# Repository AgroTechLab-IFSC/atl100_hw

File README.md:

# ATL-100 (Hardware)

**ATL-100** is a multiparametric station developed by <a href="https://agrotechlab.lages.ifsc.edu.br">AgroTechLab (*Agribusiness Technology Development Laboratory*)</a> of <a href="https://www.ifsc.edu.br">IFSC (*Federal Institute of Santa Catarina*)</a>.

It can be used as meteorological station, agrometeorological station, hydrological station, aquaculture station, tide gauge station or fire monitoring station (forest or urban environment).

It is a PTH (*Plated-Through-Hole*) project based on the ESP32-S3 MCU that aims to be easy to produce and low cost, so it uses COTS (*Commercial Off-The-Shelf*) hardware.

## Features

The current version of the ATL-100 has the following features:

### Main Board

 - Power Supply (XL4005)
   - Input: 10V ~ 30V;
   - Current: 2.5A (typ.) / 5A (max. with heat sink);
   - Efficiency: 90%
   - Frequency: 300KHz
 - Power Supply Sensor
   - Voltage Divider (30V -> 3.33V);
 - MCU (ESP32-S3)
   - RISC 32 bits 240MHz dual-core;
   - 16Mb Flash;
   - 512Kb SRAM;
   - 16Kb SRAM in RTC;
   - 8Mb PSRAM;
   - 384Kb ROM;
 - RS-485 (HW-519)
   - TTL to RS-485 converter;
   - Modbus-RTU protocol;
   - Used to connect HaliSense TH-EC-PH-NPK soil sensor:
     - Soil temperature (-40 ~ 80 ℃);
     - Soil moisture (0 ~ 100 %);
     - Soil electroconductivity (0 ~ 20.000 us/cm);
     - Soil pH (3 ~ 9 pH);
     - Soil nitrogen, phosphorus, potassium (1 ~ 1999 mg/Kg or mg/L)
 - Windsock (voltage drop based);
 - Anemometer (pulse counter based);
 - Pluviometer (pulse counter based);
 - Air sensor (BME-280)
   - Air Temperature (-40 ~ 85 ℃);
   - Air Humidity (0 ~ 100 %);
   - Atmospheric Pressure (300 ~ 1100 hPa);

### ADC Board
 - ADC (ADS1115)
   - 16 bits resolution;
   - 4 channels (4mA ~ 20mA / 0V ~ 10V);

## 3D Images

<br><hr><p style="text-align: center;">All rights reserved. &copy; Since 2020.<br><b><a href="https://agrotechlab.lages.ifsc.edu.br/">AgroTechLab (<i>Agribusiness Technology Development Laboratory</i>)</a></b><br>
<b><a href="https://ifsc.edu.br/web/campus-lages">IFSC (<i>Federal Institute of Santa Catarina</i>) - Campus Lages</a></b><br>
225 Heitor Vila Lobos St., São Francisco<br>
Lages/SC - Brazil<br>
88506-400</p>

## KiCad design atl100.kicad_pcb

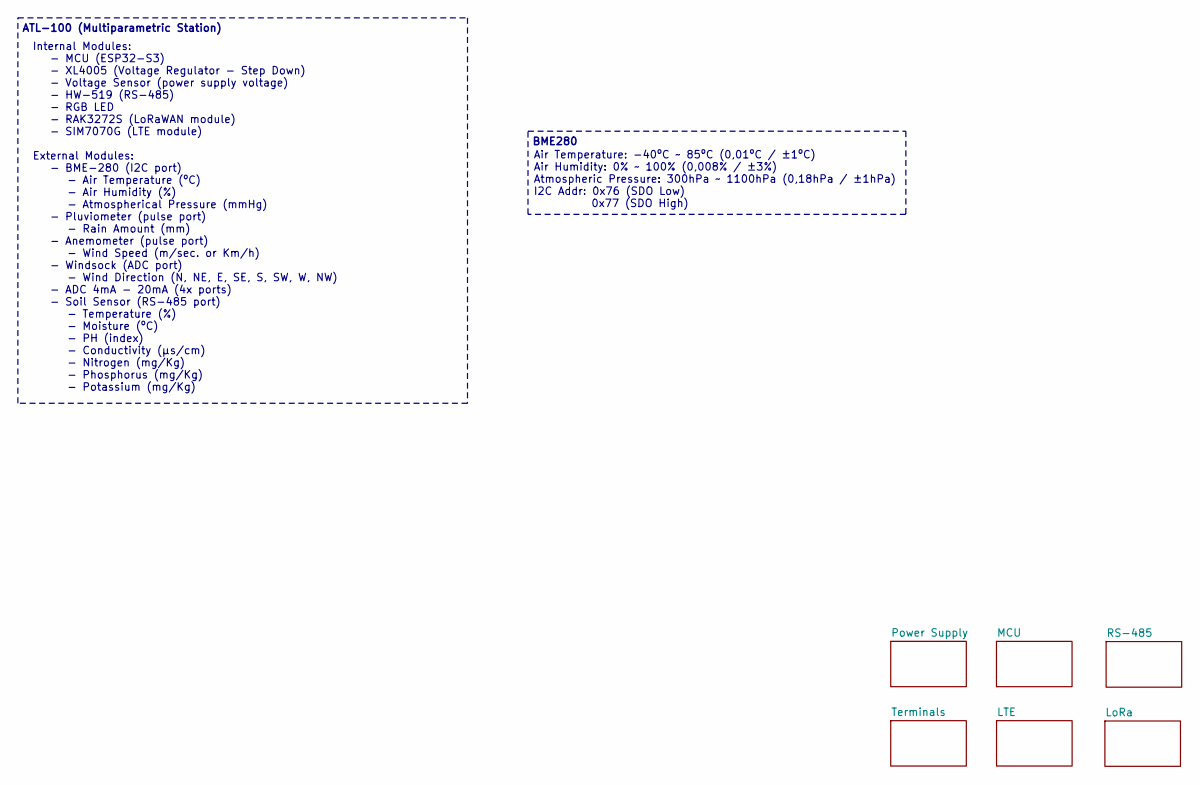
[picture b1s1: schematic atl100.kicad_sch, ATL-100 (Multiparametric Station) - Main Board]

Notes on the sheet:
BME280
Air Temperature: -40ºC ~ 85ºC (0,01ºC / ±1ºC) Air Humidity: 0% ~ 100% (0,008% / ±3%) Atmospheric Pressure: 300hPa ~ 1100hPa (0,18hPa / ±1hPa) I2C Addr: 0x76 (SDO Low) 0x77 (SDO High)
Internal Modules: - MCU (ESP32-S3) - XL4005 (Voltage Regulator - Step Down) - Voltage Sensor (power supply voltage) - HW-519 (RS-485) - RGB LED - RAK3272S (LoRaWAN module) - SIM7070G (LTE module) External Modules: - BME-280 (I2C port) - Air Temperature (ºC) - Air Humidity (%) - Atmospherical Pressu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
ATL-100 (Multiparametric Station)

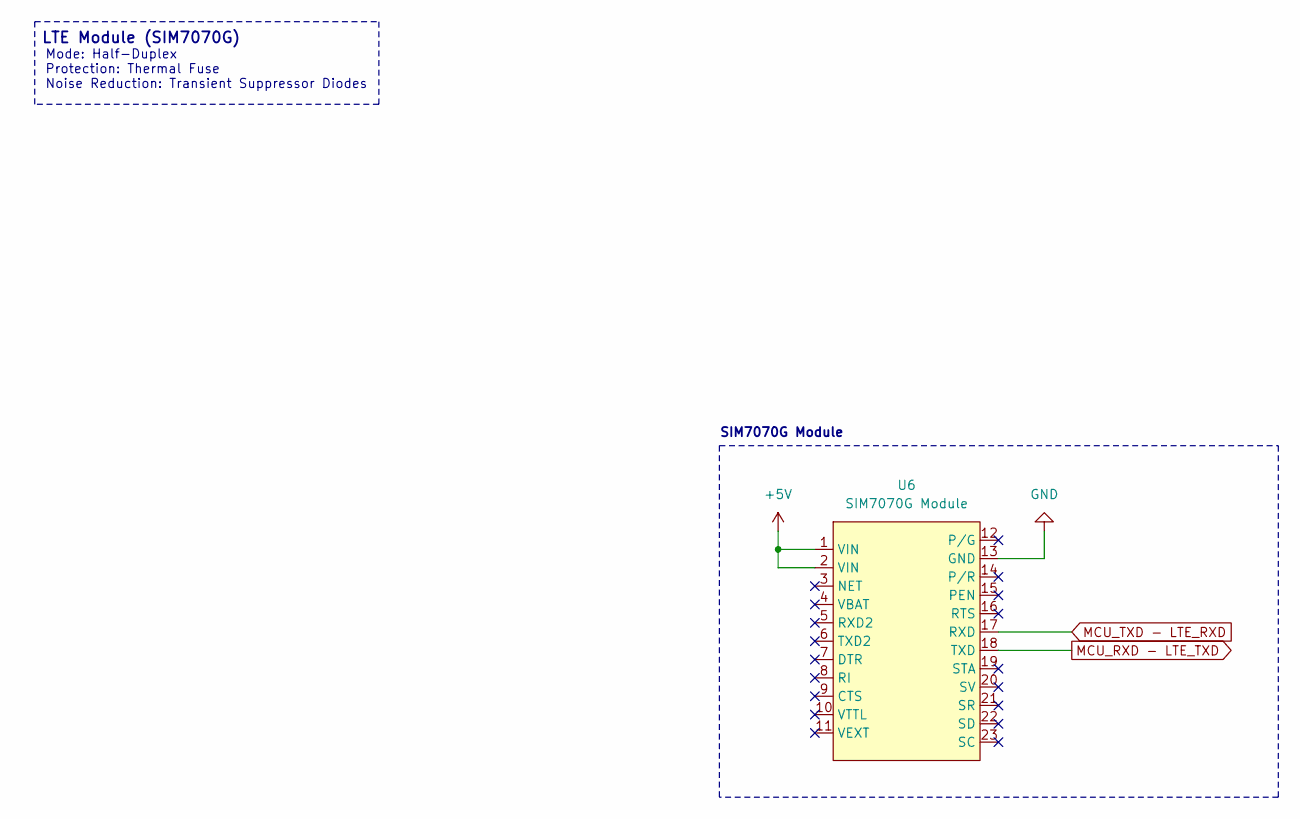
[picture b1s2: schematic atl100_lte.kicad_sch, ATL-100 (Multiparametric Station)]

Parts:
U6: SIM7070G Module; Part Number OEM

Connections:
+5V: U6.1 (VIN), U6.2 (VIN); also elsewhere on the board
GND: U6.12 (P/G), U6.13 (GND); also elsewhere on the board
LTE_PEN: U6.15 (PEN); also elsewhere on the board

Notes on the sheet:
LTE Module (SIM7070G)
SIM7070G Module
Mode: Half-Duplex Protection: Thermal Fuse Noise Reduction: Transient Suppressor Diodes

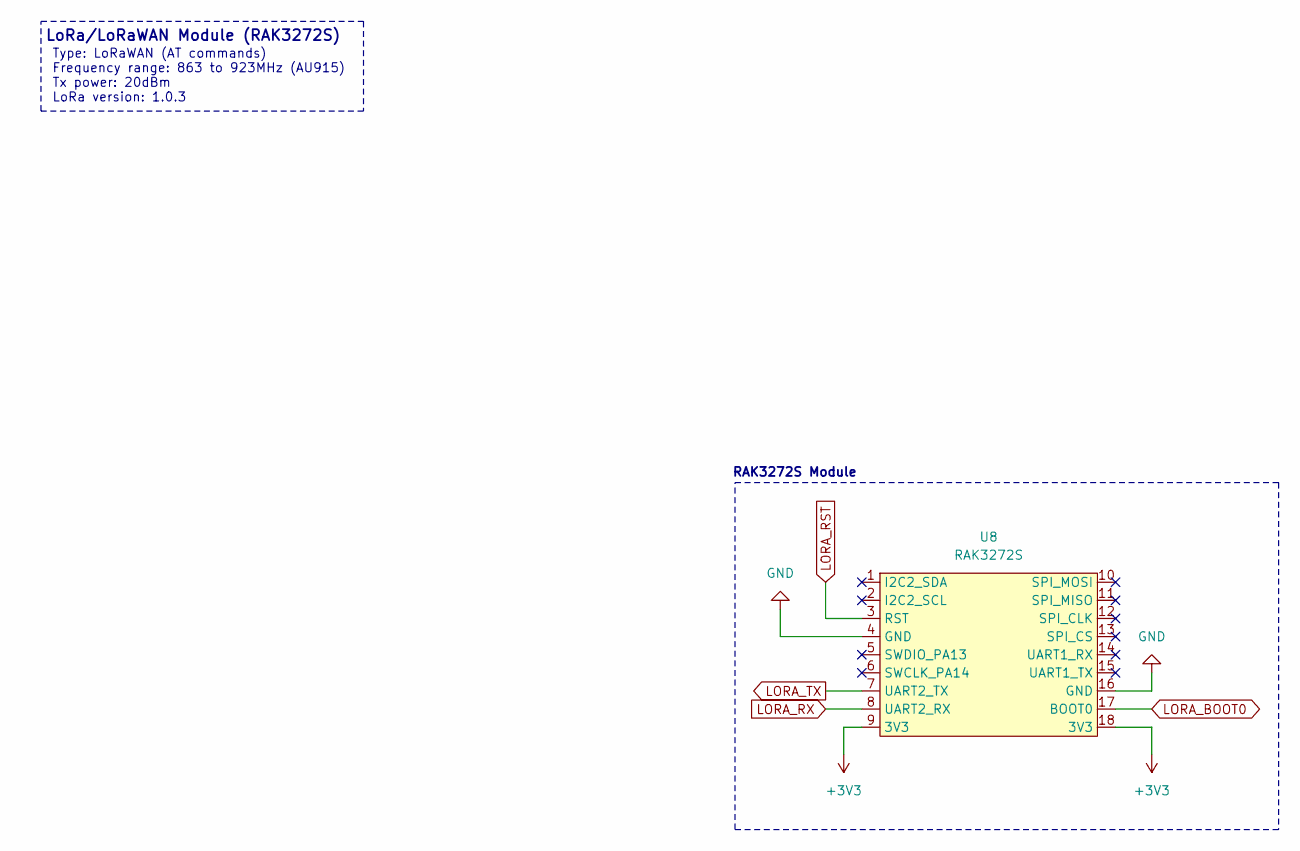
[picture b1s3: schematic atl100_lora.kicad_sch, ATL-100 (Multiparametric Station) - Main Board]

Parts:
U8: RAK3272S

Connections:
+3V3: U8.9 (3V3), U8.18 (3V3); also elsewhere on the board
GND: U8.4 (GND), U8.16 (GND); also elsewhere on the board
LORA_BOOT0: U8.17 (BOOT0); also elsewhere on the board
LORA_RST: U8.3 (RST); also elsewhere on the board
LORA_RX: U8.8 (UART2_RX); also elsewhere on the board
LORA_TX: U8.7 (UART2_TX); also elsewhere on the board

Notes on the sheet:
LoRa/LoRaWAN Module (RAK3272S)
Type: LoRaWAN (AT commands) Frequency range: 863 to 923MHz (AU915) Tx power: 20dBm LoRa version: 1.0.3
RAK3272S Module

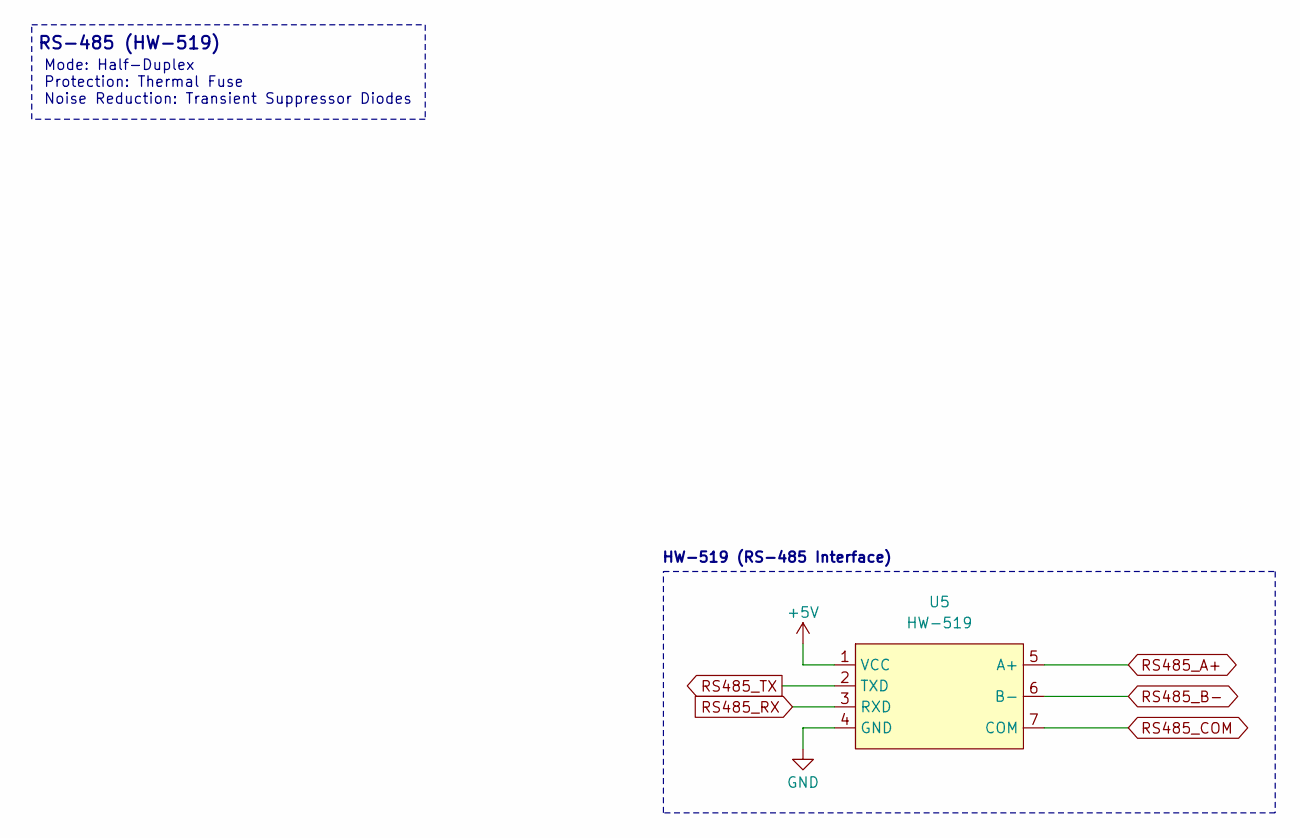
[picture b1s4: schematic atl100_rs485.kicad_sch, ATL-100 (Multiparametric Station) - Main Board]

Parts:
U5: HW-519

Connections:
+5V: U5.1 (VCC); also elsewhere on the board
GND: U5.4 (GND); also elsewhere on the board
RS485_A+: U5.5 (A+); also elsewhere on the board
RS485_B-: U5.6 (B-); also elsewhere on the board
RS485_COM: U5.7 (COM); also elsewhere on the board
RS485_RX: U5.3 (RXD); also elsewhere on the board
RS485_TX: U5.2 (TXD); also elsewhere on the board

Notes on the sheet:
RS-485 (HW-519)
Mode: Half-Duplex Protection: Thermal Fuse Noise Reduction: Transient Suppressor Diodes
HW-519 (RS-485 Interface)

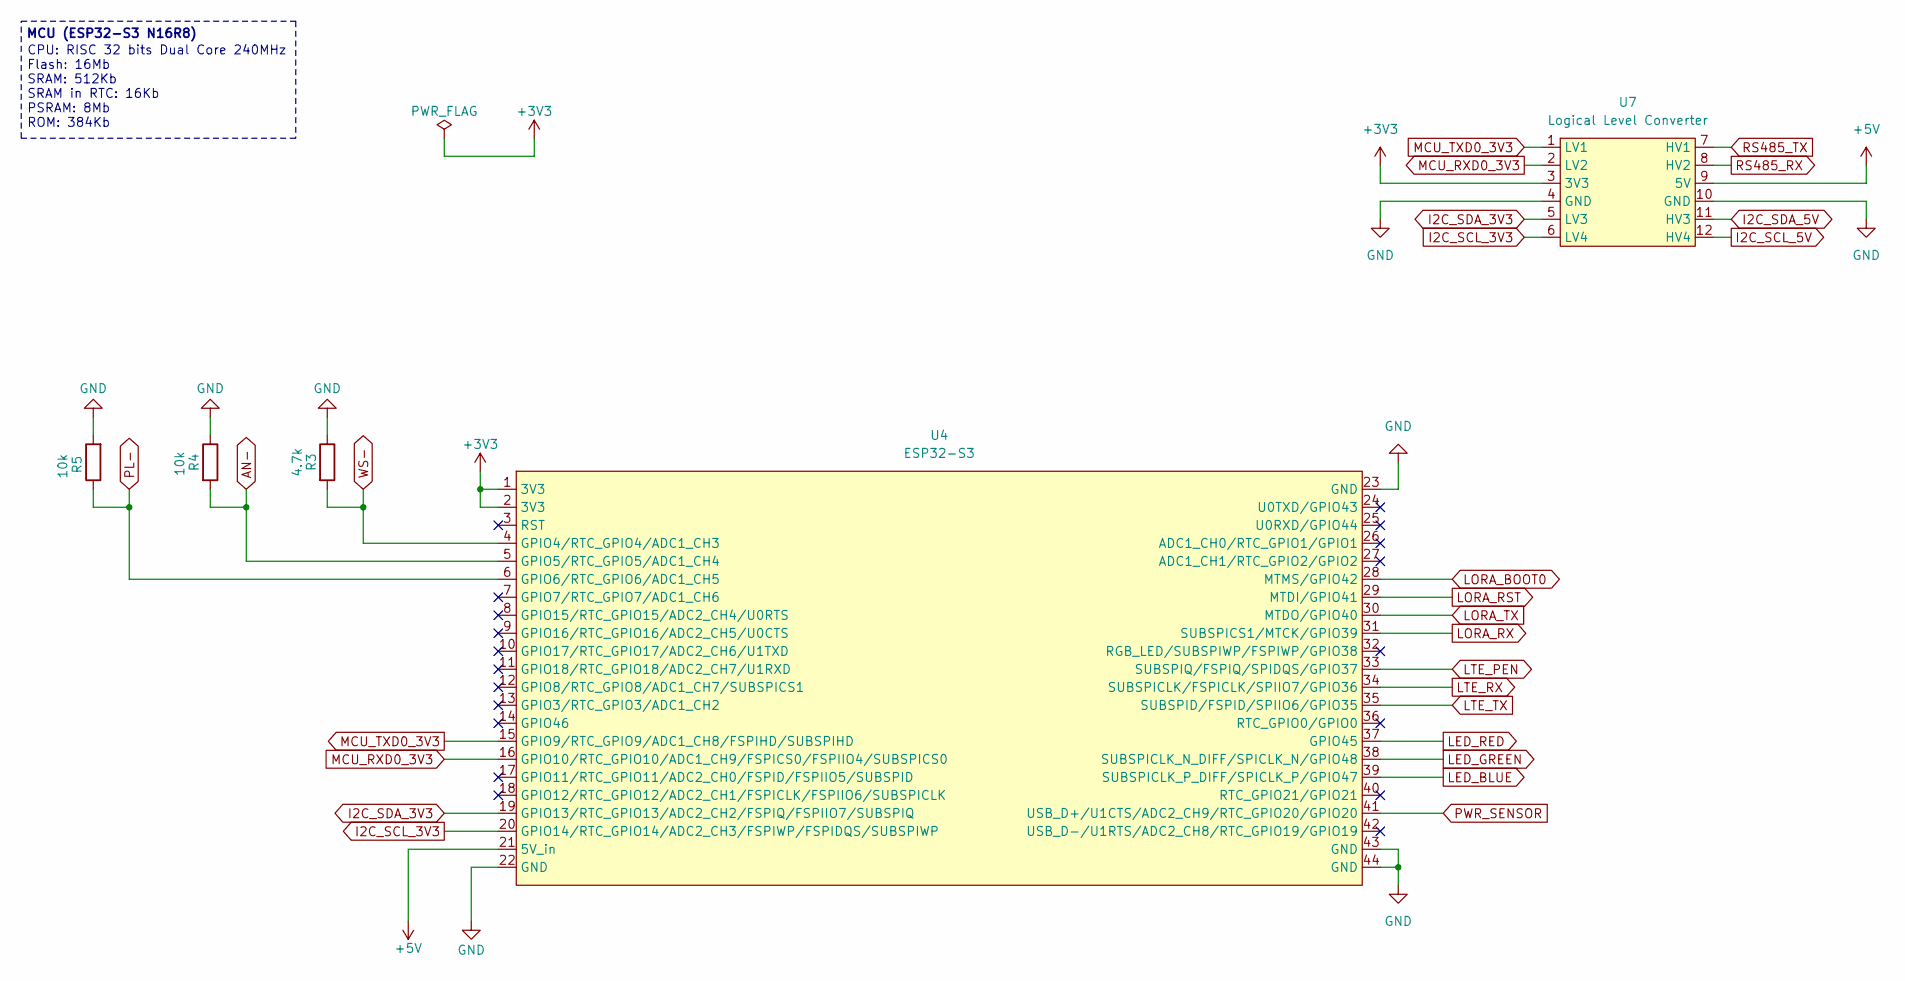
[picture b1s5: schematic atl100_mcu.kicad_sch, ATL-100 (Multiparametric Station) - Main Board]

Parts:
R3: 4.7k; R_Axial_DIN0207_L6.3mm_D2.5mm_P10.16mm_Horizontal; Part Number Std
R4, R5: 10k; R_Axial_DIN0207_L6.3mm_D2.5mm_P10.16mm_Horizontal; Part Number Std
U4: ESP32-S3; ESP32-S3 N16R8
U7: Logical Level Converter

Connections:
+3V3: U4.1 (3V3), U4.2 (3V3), U7.3 (3V3); also elsewhere on the board
+5V: U4.21 (5V_in), U7.9 (5V); also elsewhere on the board
AN-: R4.2, U4.5 (GPIO5/RTC_GPIO5/ADC1_CH4); also elsewhere on the board
GND: R3.1, R4.1, R5.2, U4.22 (GND), U4.23 (GND), U4.43 (GND), U4.44 (GND), U7.4 (GND), U7.10 (GND); also elsewhere on the board
I2C_SCL_3V3: U4.20 (GPIO14/RTC_GPIO14/ADC2_CH3/FSPIWP/FSPID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), U7.6 (LV4)
I2C_SCL_5V: U7.12 (HV4); also elsewhere on the board
I2C_SDA_3V3: U4.19 (GPIO13/RTC_GPIO13/ADC2_CH2/FSPIQ/FSPIIO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), U7.5 (LV3)
I2C_SDA_5V: U7.11 (HV3); also elsewhere on the board
LED_BLUE: U4.39 (SUBSPICLK_P_DIFF/SPICLK_P/GPIO47); also elsewhere on the board
LED_GREEN: U4.38 (SUBSPICLK_N_DIFF/SPICLK_N/GPIO48); also elsewhere on the board
LED_RED: U4.37 (GPIO45); also elsewhere on the board
LORA_BOOT0: U4.28 (MTMS/GPIO42); also elsewhere on the board
LORA_RST: U4.29 (MTDI/GPIO41); also elsewhere on the board
LORA_RX: U4.31 (SUBSPICS1/MTCK/GPIO39); also elsewhere on the board
LORA_TX: U4.30 (MTDO/GPIO40); also elsewhere on the board
LTE_PEN: U4.33 (SUBSPIQ/FSPIQ/SPIDQS/GPIO37); also elsewhere on the board
MCU_RXD0_3V3: U4.16 (GPIO10/RTC_GPIO10/ADC1_CH9/FSPICS0/FSPI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), U7.2 (LV2)
MCU_TXD0_3V3: U4.15 (GPIO9/RTC_GPIO9/ADC1_CH8/FSPIHD/SUBSPIHD), U7.1 (LV1)
PL-: R5.1, U4.6 (GPIO6/RTC_GPIO6/ADC1_CH5); also elsewhere on the board
PWR_SENSOR: U4.41 (USB_D+/U1CTS/ADC2_CH9/RTC_GPIO20/GPIO20); also elsewhere on the board
RS485_RX: U7.8 (HV2); also elsewhere on the board
RS485_TX: U7.7 (HV1); also elsewhere on the board
WS-: R3.2, U4.4 (GPIO4/RTC_GPIO4/ADC1_CH3); also elsewhere on the board

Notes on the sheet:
CPU: RISC 32 bits Dual Core 240MHz Flash: 16Mb SRAM: 512Kb SRAM in RTC: 16Kb PSRAM: 8Mb ROM: 384Kb
MCU (ESP32-S3 N16R8)

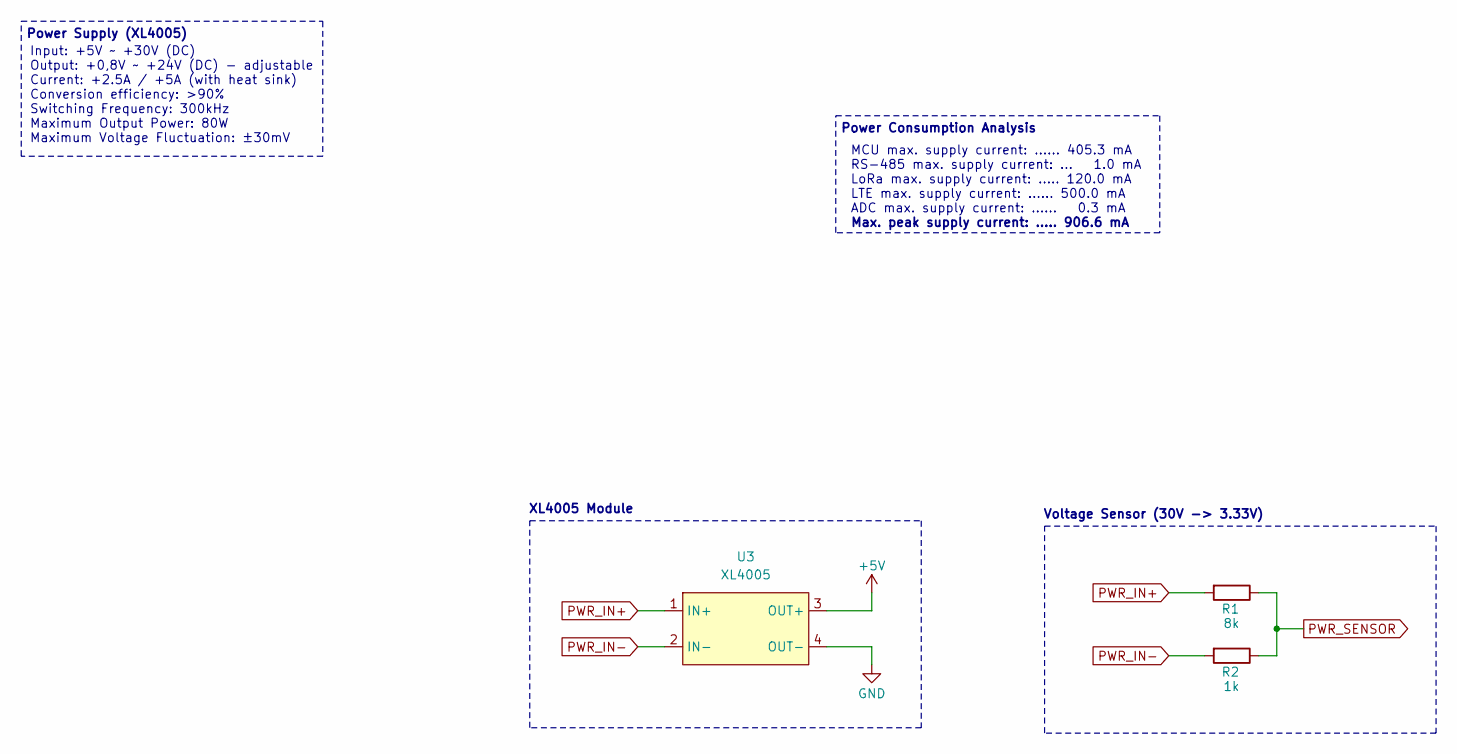
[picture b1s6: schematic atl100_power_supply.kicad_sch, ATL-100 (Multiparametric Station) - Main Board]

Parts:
R1: 8k; R_Axial_DIN0207_L6.3mm_D2.5mm_P10.16mm_Horizontal; Part Number Std
R2: 1k; R_Axial_DIN0207_L6.3mm_D2.5mm_P10.16mm_Horizontal; Part Number Std
U3: XL4005; Part Number Std

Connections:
+5V: U3.3 (OUT+); also elsewhere on the board
GND: U3.4 (OUT-); also elsewhere on the board
PWR_IN+: R1.2, U3.1 (IN+); also elsewhere on the board
PWR_IN-: R2.2, U3.2 (IN-); also elsewhere on the board
PWR_SENSOR: R1.1, R2.1; also elsewhere on the board

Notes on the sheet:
Voltage Sensor (30V -> 3.33V)
XL4005 Module
Max. peak supply current: ..... 906.6 mA
MCU max. supply current: ...... 405.3 mA RS-485 max. supply current: ... 1.0 mA LoRa max. supply current: ..... 120.0 mA LTE max. supply current: ...... 500.0 mA ADC max. supply current: ...... 0.3 mA
Input: +5V ~ +30V (DC) Output: +0,8V ~ +24V (DC) - adjustable Current: +2.5A / +5A (with heat sink) Conversion efficiency: >90% Switching Frequency: 300kHz Maximum Output Power: 80W Maximum Voltage Fluctuation: ±30mV
Power Consumption Analysis
Power Supply (XL4005)

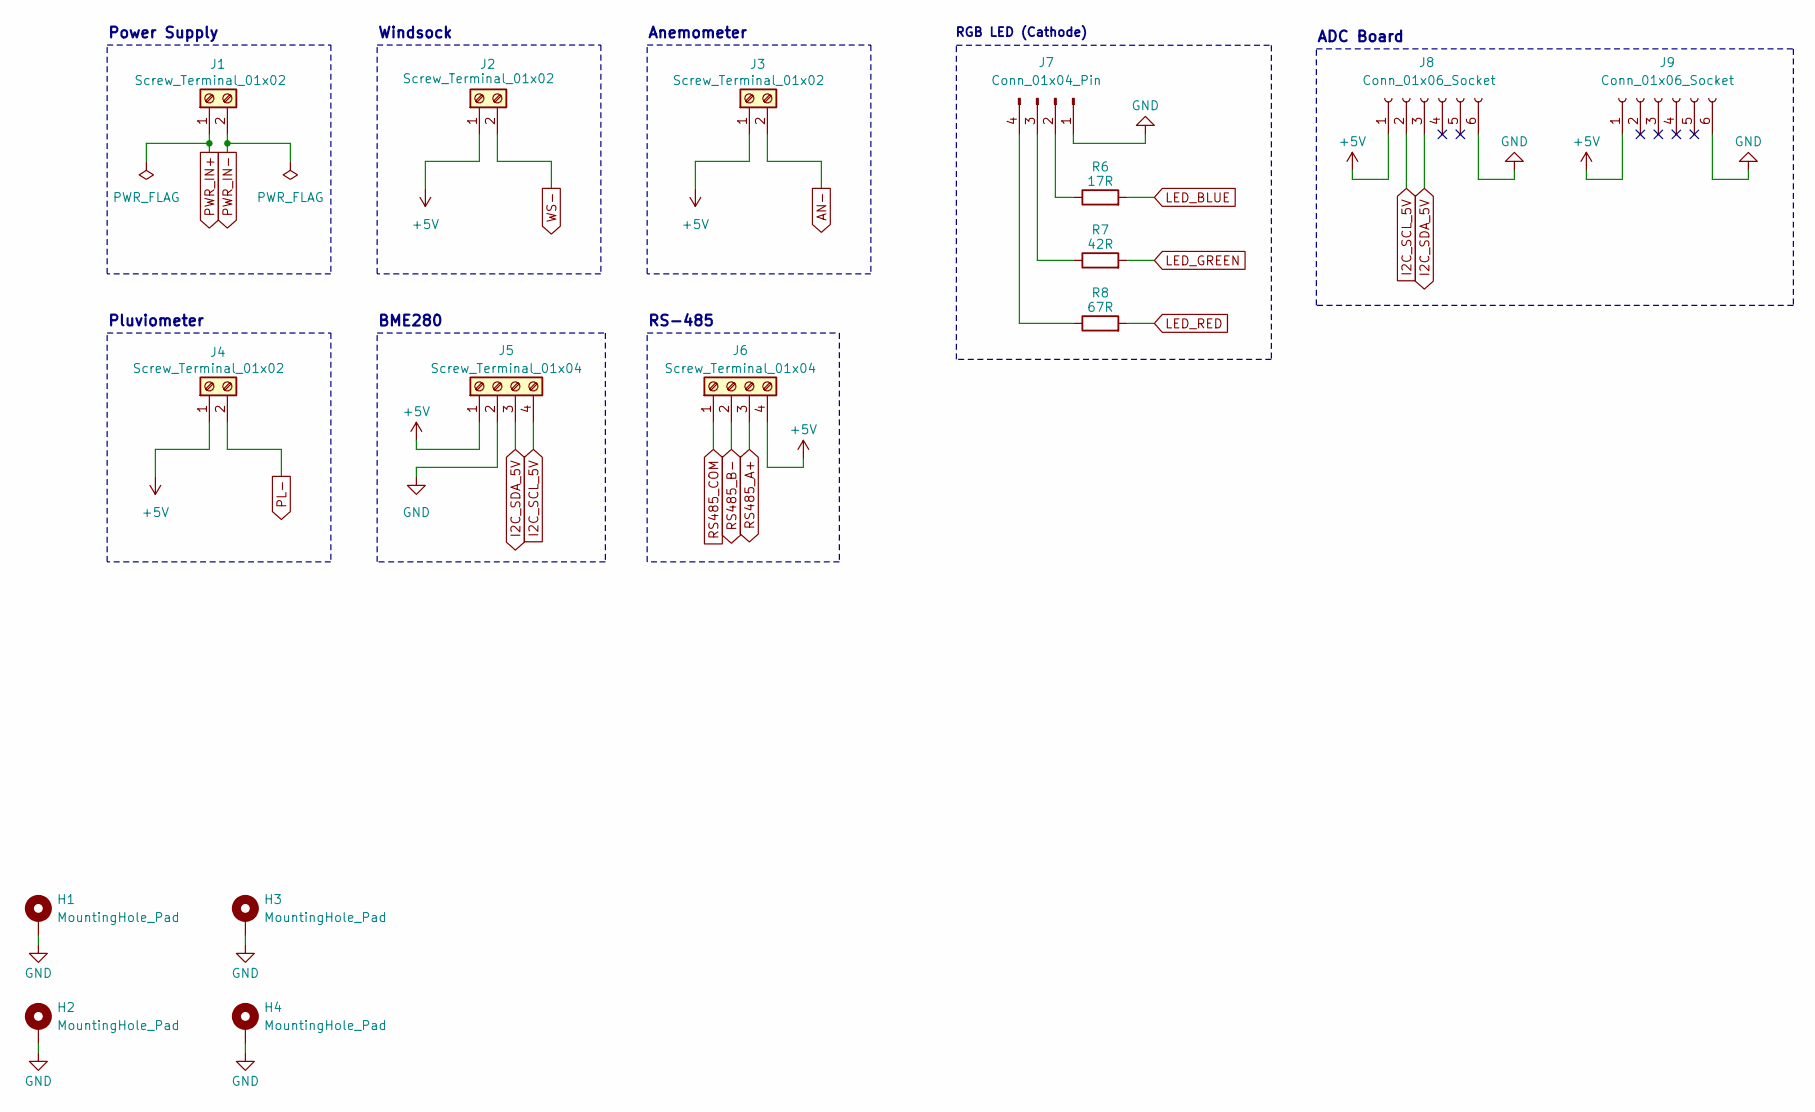
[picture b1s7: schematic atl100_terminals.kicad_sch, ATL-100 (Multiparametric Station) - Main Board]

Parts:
H1, H2, H3, H4: MountingHole_Pad; MountingHole_2.2mm_M2_Pad_Via
J1, J2, J3, J4: Screw_Terminal_01x02; TerminalBlock_Phoenix_MKDS-1,5-2-5.08_1x02_P5.08mm_Horizont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; Part Number Std
J5, J6: Screw_Terminal_01x04; TerminalBlock_Phoenix_MKDS-1,5-4-5.08_1x04_P5.08mm_Horizont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; Part Number Std
J7: Conn_01x04_Pin; PinHeader_1x04_P2.54mm_Horizontal
J8, J9: Conn_01x06_Socket; PinSocket_1x06_P2.54mm_Vertical
R6: 17R; R_Axial_DIN0207_L6.3mm_D2.5mm_P10.16mm_Horizontal; Part Number Std
R7: 42R; R_Axial_DIN0207_L6.3mm_D2.5mm_P10.16mm_Horizontal; Part Number Std
R8: 67R; R_Axial_DIN0207_L6.3mm_D2.5mm_P10.16mm_Horizontal; Part Number Std

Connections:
+5V: J2.1, J3.1, J4.1, J5.1, J6.4, J8.1, J9.1; also elsewhere on the board
AN-: J3.2; also elsewhere on the board
GND: H1.1, H2.1, H3.1, H4.1, J5.2, J7.1, J8.6, J9.6; also elsewhere on the board
I2C_SCL_5V: J5.4, J8.2; also elsewhere on the board
I2C_SDA_5V: J5.3, J8.3; also elsewhere on the board
LED_BLUE: R6.2; also elsewhere on the board
LED_GREEN: R7.2; also elsewhere on the board
LED_RED: R8.2; also elsewhere on the board
unnamed: J7.2, R6.1
unnamed: J7.3, R7.1
unnamed: J7.4, R8.1
PL-: J4.2; also elsewhere on the board
PWR_IN+: J1.1; also elsewhere on the board
PWR_IN-: J1.2; also elsewhere on the board
RS485_A+: J6.3; also elsewhere on the board
RS485_B-: J6.2; also elsewhere on the board
RS485_COM: J6.1; also elsewhere on the board
WS-: J2.2; also elsewhere on the board

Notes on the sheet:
Anemometer
Windsock
Pluviometer
ADC Board
Power Supply
BME280
RS-485
RGB LED (Cathode)

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
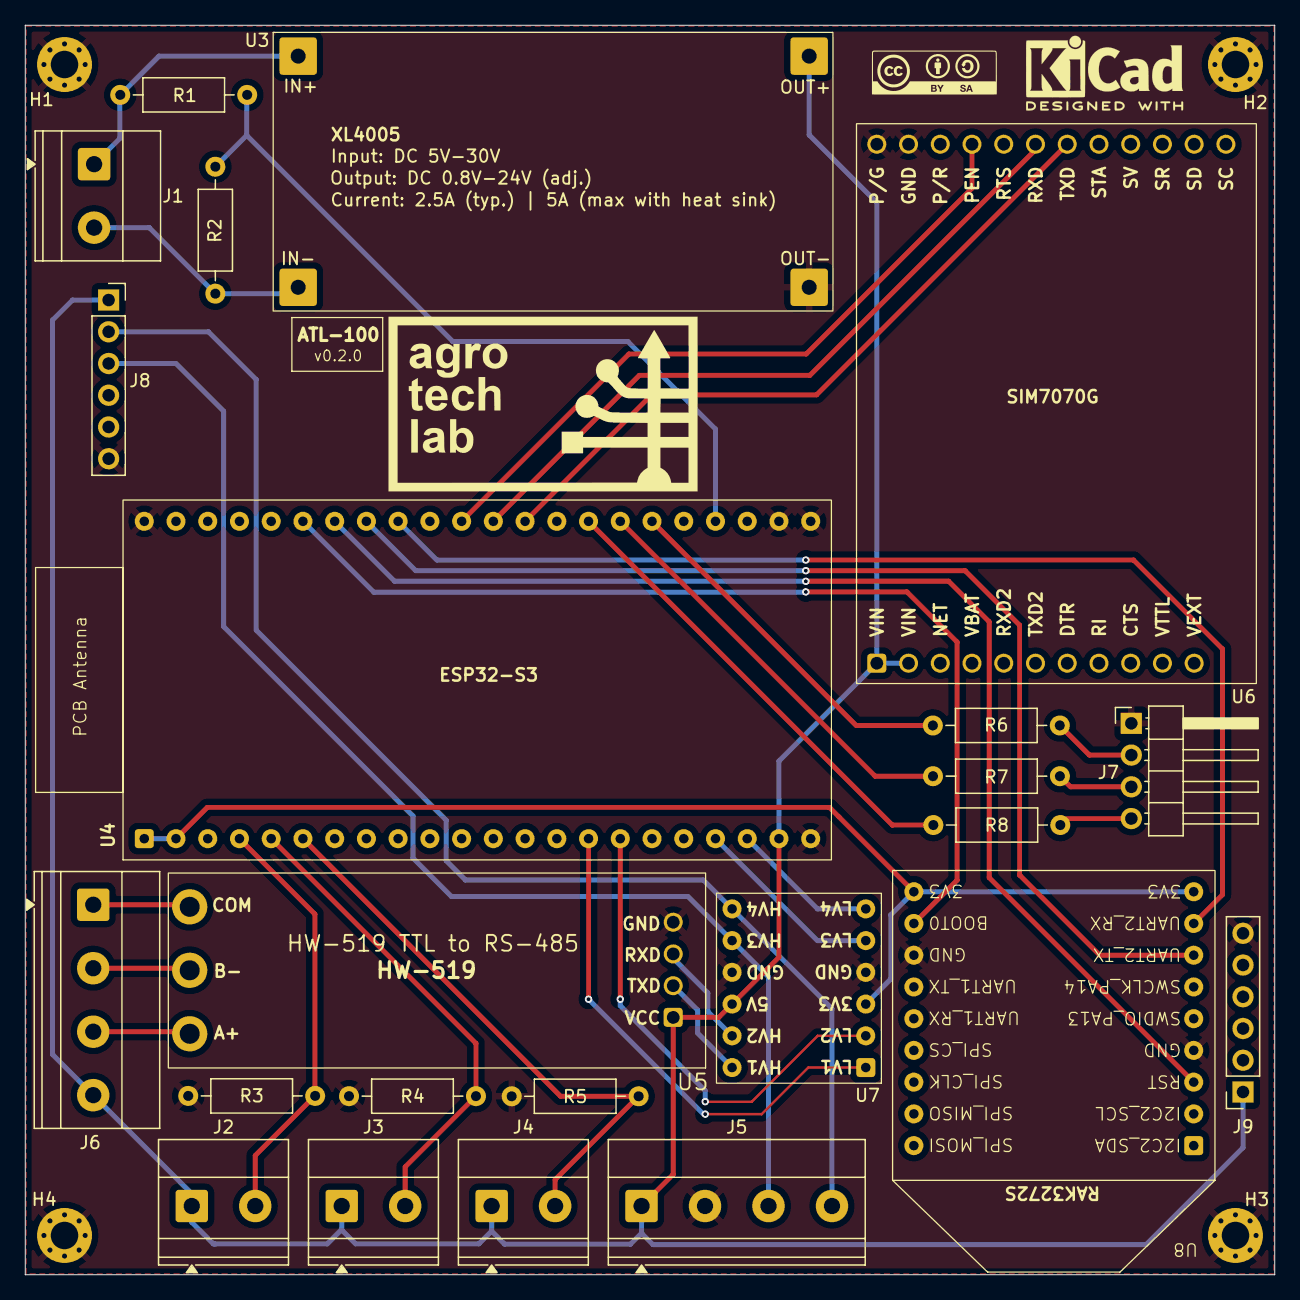
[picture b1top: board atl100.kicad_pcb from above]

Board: 2 copper layers, 100.0 x 100.0 mm, 30 parts (0 on the bottom side), 33 nets.

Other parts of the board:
agrotechlab_logo: Logo AgroTechLab
cc_by_sa_logo: Logo CC-BY-SA
kicad_logo: KiCad-Logo2_5mm_SilkScreen

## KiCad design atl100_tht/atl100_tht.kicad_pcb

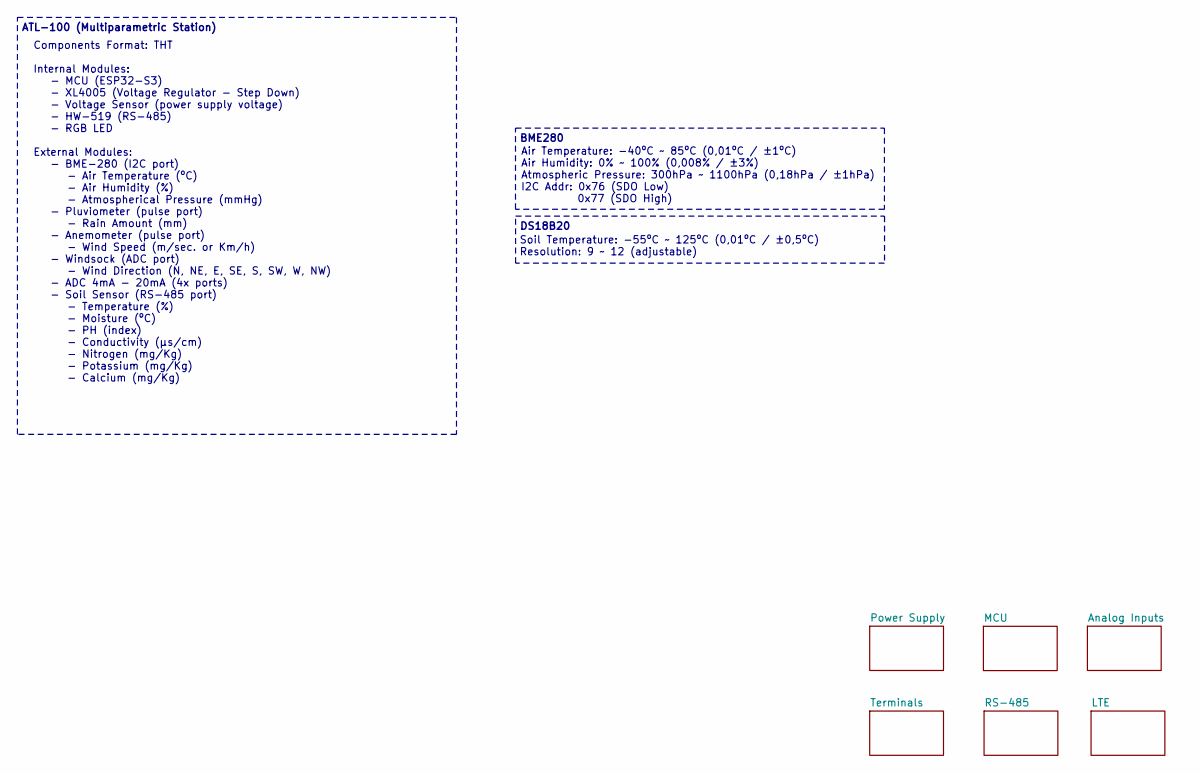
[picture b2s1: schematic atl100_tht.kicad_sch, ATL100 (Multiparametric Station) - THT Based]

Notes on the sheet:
Soil Temperature: -55ºC ~ 125ºC (0,01ºC / ±0,5ºC) Resolution: 9 ~ 12 (adjustable)
DS18B20
BME280
Air Temperature: -40ºC ~ 85ºC (0,01ºC / ±1ºC) Air Humidity: 0% ~ 100% (0,008% / ±3%) Atmospheric Pressure: 300hPa ~ 1100hPa (0,18hPa / ±1hPa) I2C Addr: 0x76 (SDO Low) 0x77 (SDO High)
Components Format: THT Internal Modules: - MCU (ESP32-S3) - XL4005 (Voltage Regulator - Step Down) - Voltage Sensor (power supply voltage) - HW-519 (RS-485) - RGB LED External Modules: - BME-280 (I2C port) - Air Temperature (ºC) - Air Humidity (%) - Atmospherical Pressure (mmHg) - Pluviometer (puls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
ATL-100 (Multiparametric Station)

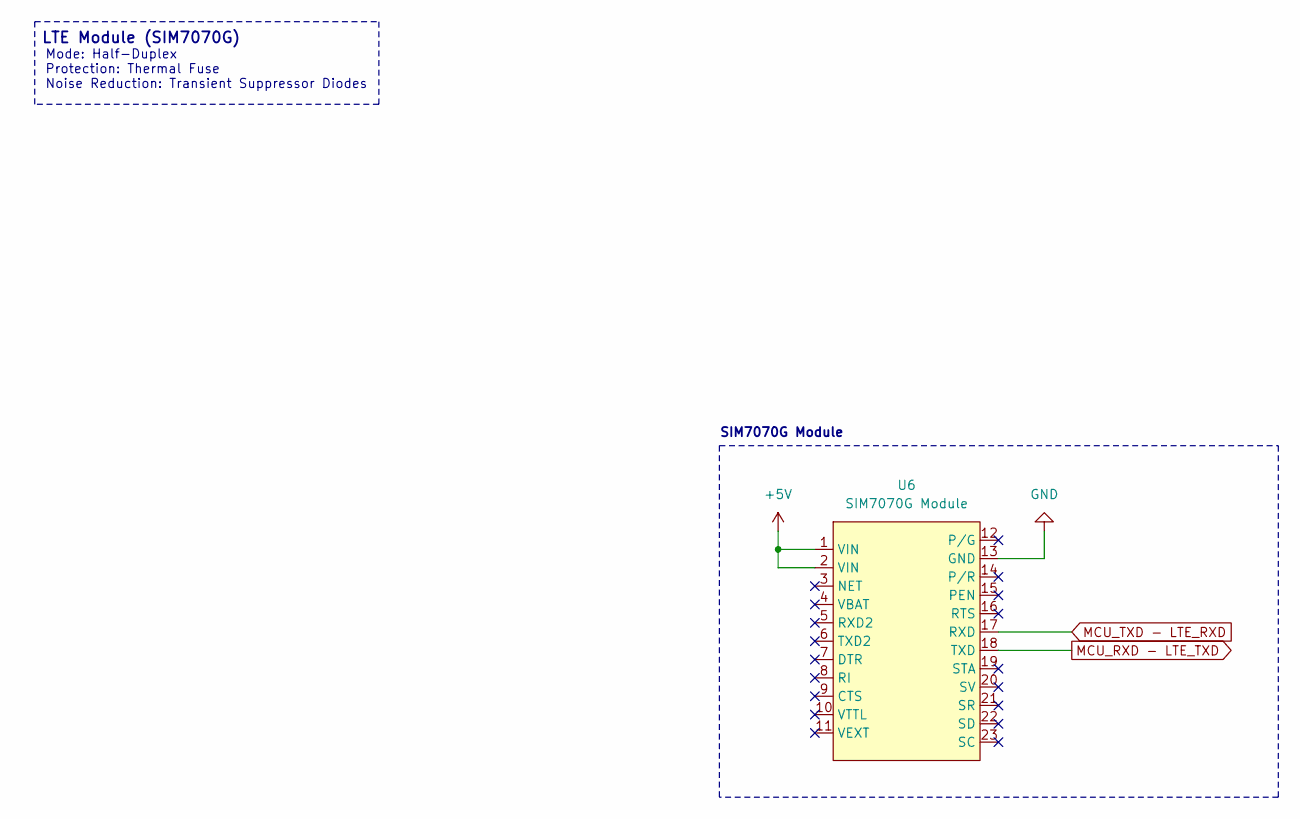
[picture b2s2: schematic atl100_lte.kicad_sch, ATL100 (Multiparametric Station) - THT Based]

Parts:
U6: SIM7070G Module; Part Number OEM

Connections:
+5V: U6.1 (VIN), U6.2 (VIN); also elsewhere on the board
GND: U6.13 (GND); also elsewhere on the board
MCU_RXD - LTE_TXD: U6.18 (TXD); also elsewhere on the board
MCU_TXD - LTE_RXD: U6.17 (RXD); also elsewhere on the board

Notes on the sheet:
LTE Module (SIM7070G)
SIM7070G Module
Mode: Half-Duplex Protection: Thermal Fuse Noise Reduction: Transient Suppressor Diodes

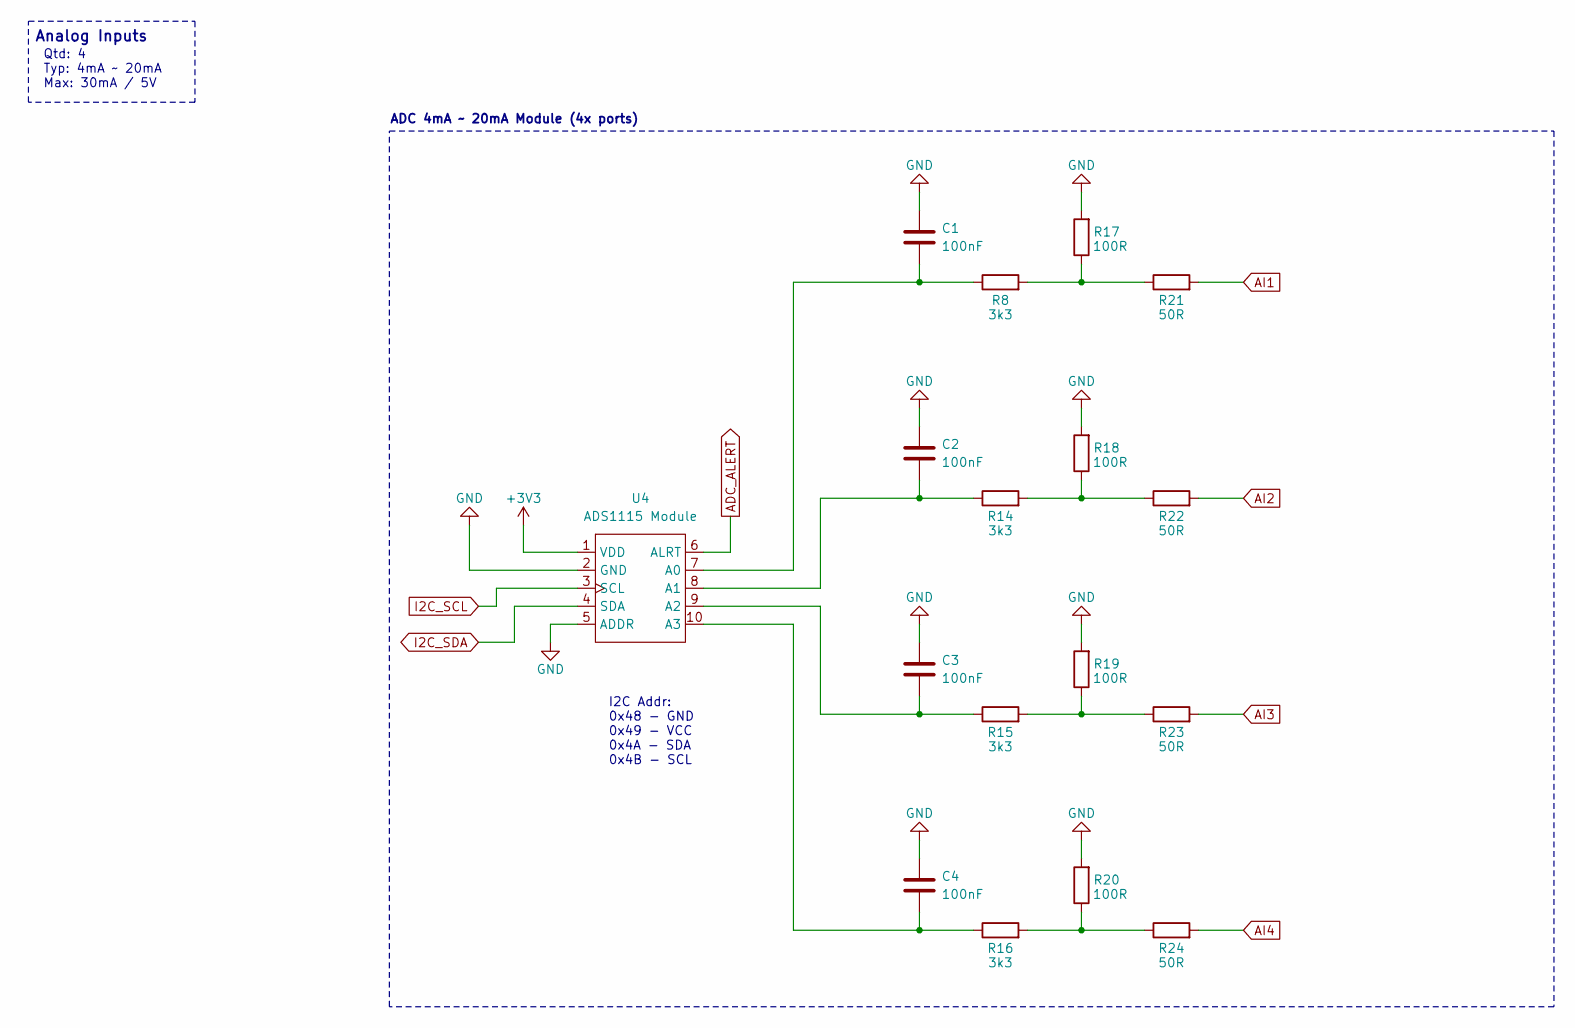
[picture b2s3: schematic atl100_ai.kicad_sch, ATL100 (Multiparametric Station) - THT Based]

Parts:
C1, C2, C3, C4: 100nF; C_Disc_D4.7mm_W2.5mm_P5.00mm; Part Number Std
R8, R14, R15, R16: 3k3; R_Axial_DIN0207_L6.3mm_D2.5mm_P7.62mm_Horizontal; Part Number Std
R17, R18, R19, R20: 100R; R_Axial_DIN0207_L6.3mm_D2.5mm_P7.62mm_Horizontal; Part Number Std
R21, R22, R23, R24: 50R; R_Axial_DIN0207_L6.3mm_D2.5mm_P7.62mm_Horizontal; Part Number Std
U4: ADS1115 Module; Part Number ADS1115 Module

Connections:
+3V3: U4.1 (VDD); also elsewhere on the board
ADC_ALERT: U4.6 (ALRT); also elsewhere on the board
AI1: R21.2; also elsewhere on the board
AI2: R22.2; also elsewhere on the board
AI3: R23.2; also elsewhere on the board
AI4: R24.2; also elsewhere on the board
GND: C1.1, C2.1, C3.1, C4.1, R17.2, R18.2, R19.2, R20.2, U4.2 (GND), U4.5 (ADDR); also elsewhere on the board
I2C_SCL: U4.3 (SCL); also elsewhere on the board
I2C_SDA: U4.4 (SDA); also elsewhere on the board
unnamed: R14.2, R18.1, R22.1
unnamed: R15.2, R19.1, R23.1
unnamed: R16.2, R20.1, R24.1
unnamed: R8.2, R17.1, R21.1
unnamed: C1.2, R8.1, U4.7 (A0)
unnamed: C2.2, R14.1, U4.8 (A1)
unnamed: C3.2, R15.1, U4.9 (A2)
unnamed: C4.2, R16.1, U4.10 (A3)

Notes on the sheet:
ADC 4mA ~ 20mA Module (4x ports)
I2C Addr: 0x48 - GND 0x49 - VCC 0x4A - SDA 0x4B - SCL
Qtd: 4 Typ: 4mA ~ 20mA Max: 30mA / 5V
Analog Inputs

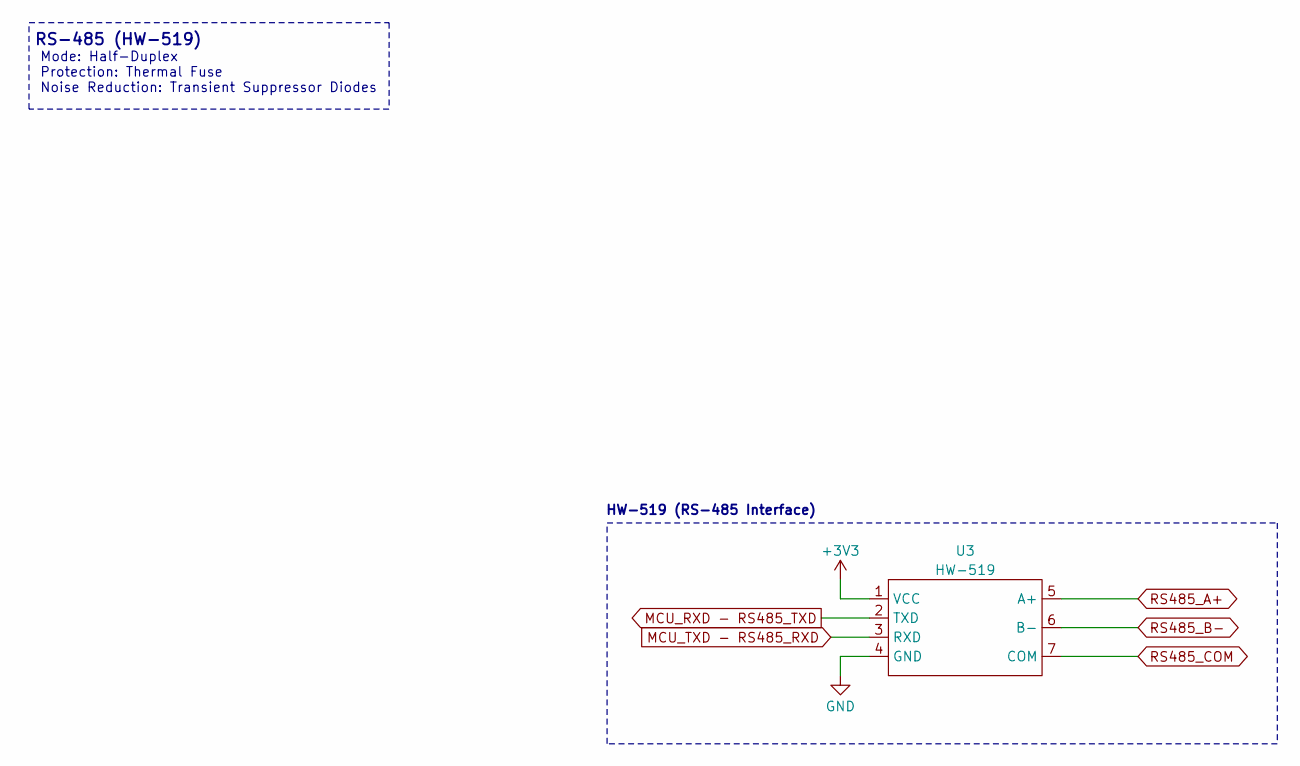
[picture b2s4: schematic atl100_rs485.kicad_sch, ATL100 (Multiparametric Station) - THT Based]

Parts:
U3: HW-519; Part Number HW-519

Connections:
+3V3: U3.1 (VCC); also elsewhere on the board
GND: U3.4 (GND); also elsewhere on the board
MCU_RXD - RS485_TXD: U3.2 (TXD); also elsewhere on the board
MCU_TXD - RS485_RXD: U3.3 (RXD); also elsewhere on the board
RS485_A+: U3.5 (A+); also elsewhere on the board
RS485_B-: U3.6 (B-); also elsewhere on the board
RS485_COM: U3.7 (COM); also elsewhere on the board

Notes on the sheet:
RS-485 (HW-519)
Mode: Half-Duplex Protection: Thermal Fuse Noise Reduction: Transient Suppressor Diodes
HW-519 (RS-485 Interface)

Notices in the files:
atl100.kicad_pcb:
Licensed under CC-BY-SA 4.0
